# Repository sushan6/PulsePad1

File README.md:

# PulsePad

PulsePad is an ultra-compact, open-source 4-key macropad powered by the **Seeed Studio XIAO RP2040** microcontroller.

I wanted to make a small macropad with four mechanical switches that could be used for shortcuts and other frequently used actions. I designed the PCB and schematic in KiCad and also worked on a 3D enclosure to fit the board.

The design uses the XIAO RP2040 as the main controller, with four mechanical switches connected to it. The idea is to keep everything compact without making the PCB or enclosure unnecessarily complicated.

## Features

- 4 mechanical switches
- Seeed Studio XIAO RP2040 microcontroller
- Custom PCB designed in KiCad
- Custom 3D enclosure
- Compact design
- Open-source hardware

# 3D Model

This is the overall 3D model of PulsePad, showing how the PCB, switches, keycaps, and enclosure fit together.

# 3D Front View of PCB

# 3D Back View of PCB

# PCB

The PCB contains the four mechanical switch positions and the footprint for the XIAO RP2040. I designed the layout in KiCad and arranged the components to keep the board as compact as possible.

# Schematics

The schematic shows the connections between the four mechanical switches and the XIAO RP2040.

# How It Works

The XIAO RP2040 is responsible for reading the inputs from the four mechanical switches.

Each switch is connected to a GPIO pin on the microcontroller. When a key is pressed, the RP2040 can detect the input and the firmware can use it to trigger a keyboard shortcut or another assigned action.

The keys can be configured for different functions depending on how the firmware is set up.

# Enclosure

I also designed a 3D enclosure for the PCB. It is made to fit the board and switches while keeping the overall size small.

The enclosure can be 3D printed and modified if any adjustments to the design are needed.

# Design Files

The project includes the KiCad schematic and PCB design files, along with the 3D model of the board and enclosure.

These files can be used to inspect the design, make changes, or manufacture your own PulsePad.

## Acknowledgements

This project was designed using **KiCad EDA**. Thanks to the KiCad developers and the open-source community for making such a useful tool available for hardware design.

---

## License

This project is open-source. Feel free to modify, manufacture, and adapt it for your own personal use!

---

## Bill of Materials (BOM)

The following table contains the components required to build one PulsePad, along with their footprints, quantities, purchase links, and estimated prices.

## Bill of Materials (BOM)

### Main BOM

| **Item** | **Link** | **Quantity** | **Cost (USD)** | **Notes** |
|---|---|---:|---:|---|
| Seeed Studio XIAO RP2040 | [Robu.in](https://robu.in/product/seeed-studio-xiao-rp2040-v1-0/) | 2 | $13 | $6.5 each |
| Mechanical switches | [Amazon.in](https://www.amazon.in/dp/B0HJYNT2W7) | 1 pack | $7 | Pack of 40 |
| Gradient keycaps | [Amazon.in](https://www.amazon.in/dp/B0HGLWF4Q1) | 1 pack | $11 | 133-piece set |
| Custom PCB | [JLCPCB](https://jlcpcb.com/) | 5 | $12.00 | PCB fabrication |
| Enclosures | N/A | 5 | $0.00 | Self-printed |

### Cost Summary

| **Item** | **Cost (USD)** |
|---|---:|     
| XIAO RP2040 | $13 |
| Mechanical switches | $7 |
| Gradient keycaps | $11 |
| PCB fabrication | $12.00 |
| Enclosures | $0.00 |
| **Total** | **$43** |

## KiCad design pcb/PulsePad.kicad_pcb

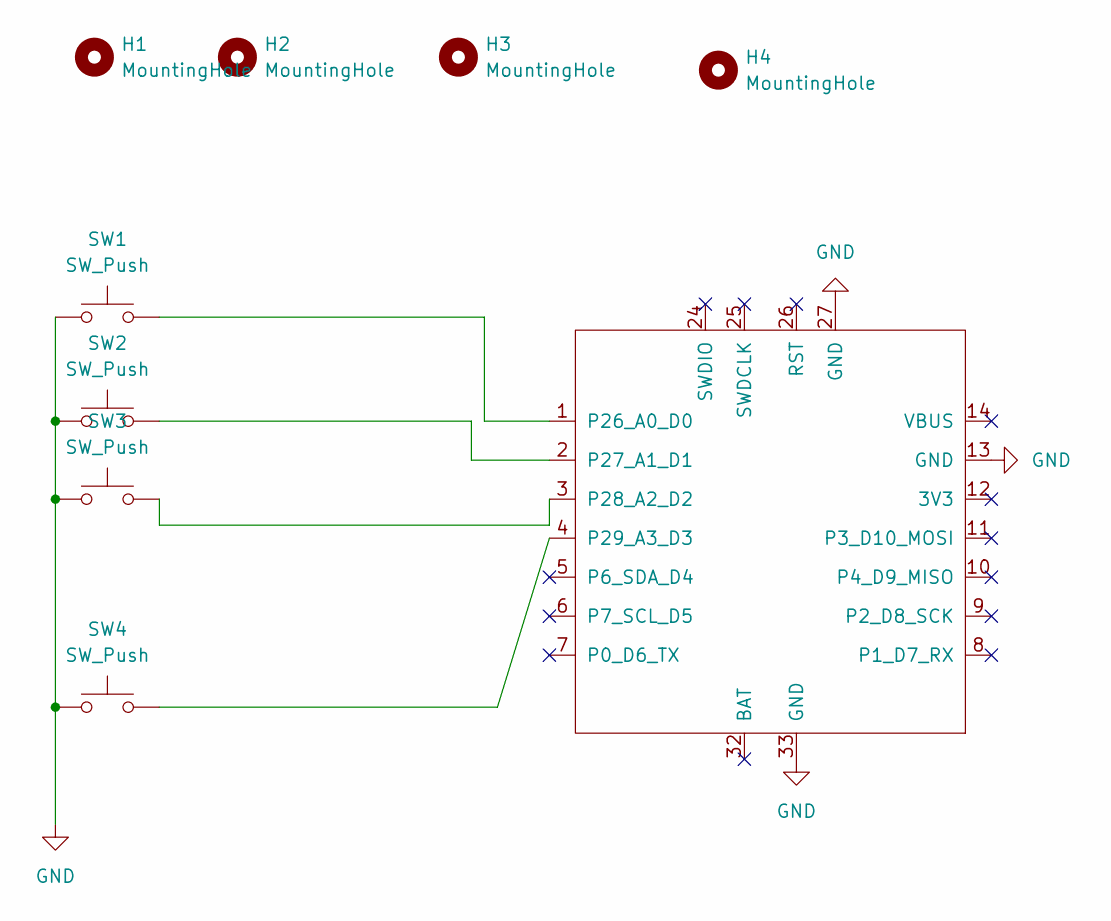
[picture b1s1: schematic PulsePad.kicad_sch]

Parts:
H1, H2, H3, H4: MountingHole; MountingHole_2.1mm
SW1, SW2, SW3, SW4: SW_Push; SW_Cherry_MX_1.00u_PCB
U1: XIAO-RP2040-SMD; XIAO-RP2040-SMD (1)

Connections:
GND: SW1.1, SW2.1, SW3.1, SW4.1, U1.13 (GND), U1.27 (GND), U1.33 (GND)
unnamed: SW1.2, U1.1 (P26_A0_D0)
unnamed: SW2.2, U1.2 (P27_A1_D1)
unnamed: SW3.2, U1.3 (P28_A2_D2)
unnamed: SW4.2, U1.4 (P29_A3_D3)

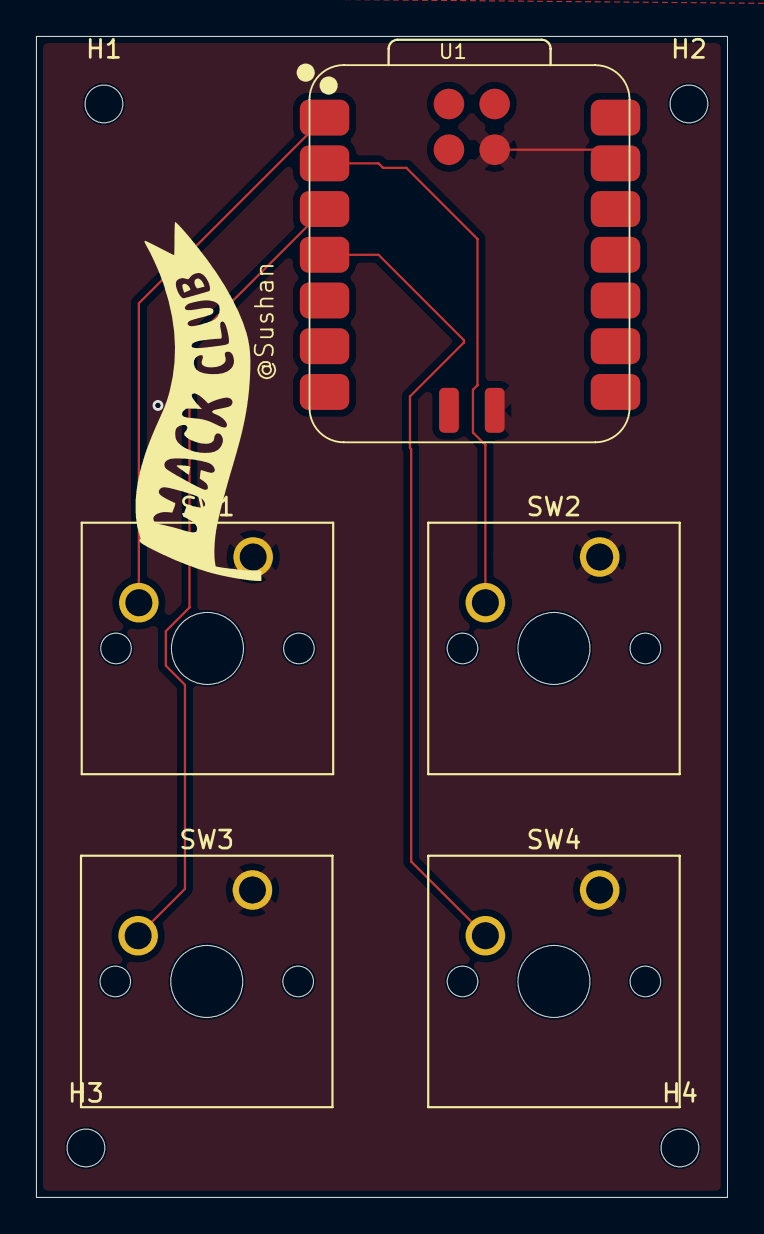
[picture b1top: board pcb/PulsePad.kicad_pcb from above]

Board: 4 copper layers, 38.4 x 64.5 mm, 9 parts (0 on the bottom side), 5 nets.

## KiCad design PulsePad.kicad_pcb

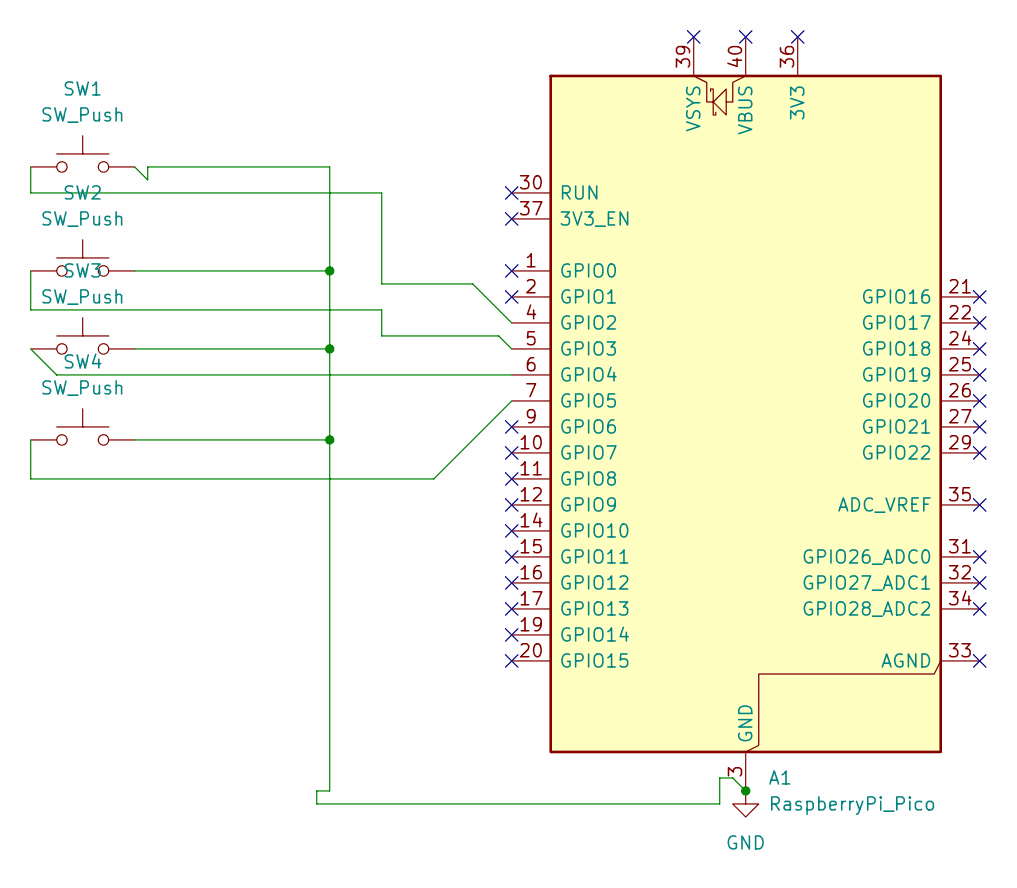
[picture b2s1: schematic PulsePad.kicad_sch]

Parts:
A1: RaspberryPi_Pico; RaspberryPi_Pico_Common_Unspecified
SW1, SW2, SW3, SW4: SW_Push; SW_Cherry_MX_1.00u_PCB

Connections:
GND: A1.3 (GND), A1.8 (GND), A1.13 (GND), A1.18 (GND), A1.23 (GND), A1.28 (GND), A1.38 (GND), SW1.2, SW2.2, SW3.2, SW4.2
unnamed: A1.4 (GPIO2), SW1.1
unnamed: A1.5 (GPIO3), SW2.1
unnamed: A1.6 (GPIO4), SW3.1
unnamed: A1.7 (GPIO5), SW4.1

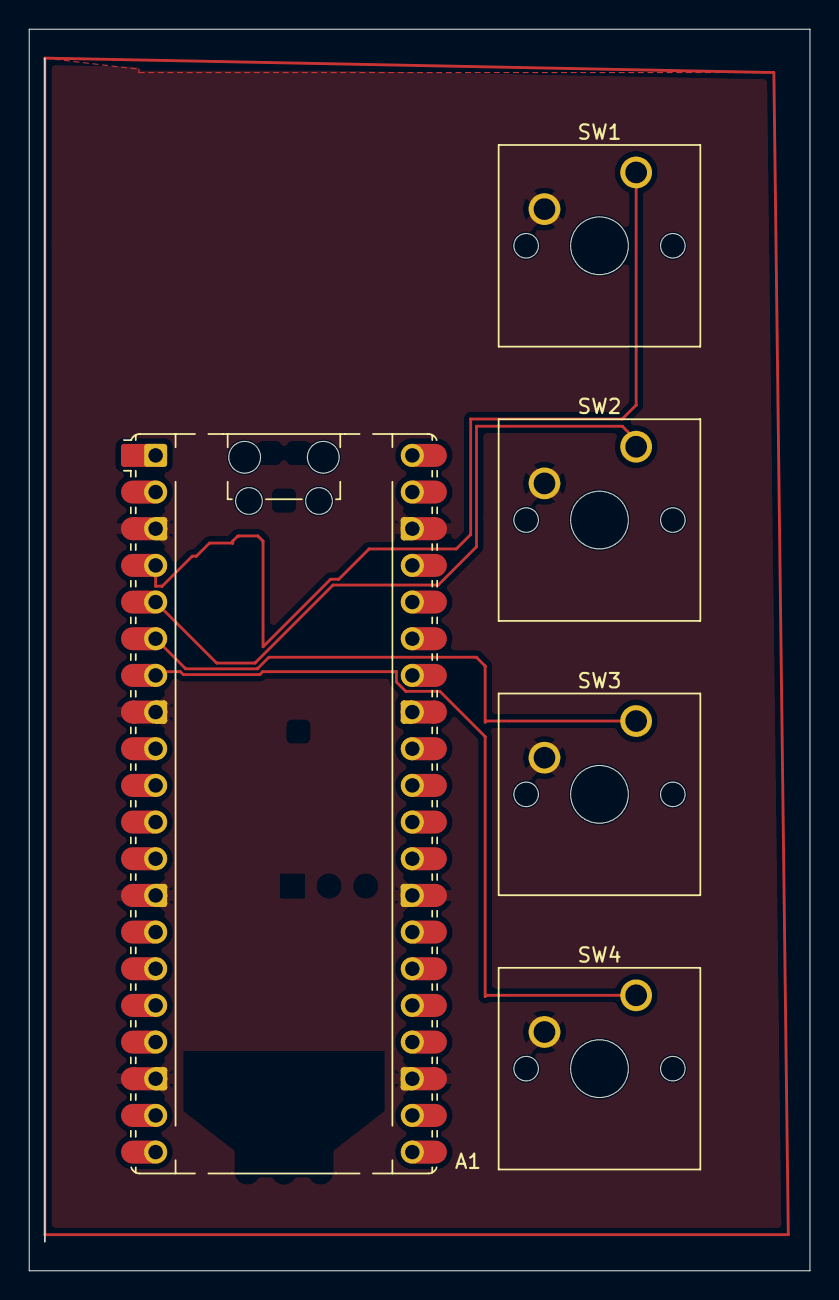
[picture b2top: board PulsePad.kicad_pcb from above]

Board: 4 copper layers, 54.1 x 86.0 mm, 5 parts (0 on the bottom side), 5 nets.

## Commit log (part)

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2026-05-29 Update README with images and project details
    Added images and improved project description.
2026-06-28 Adding FIles
2026-06-28 Enhance README with project details and acknowledgements
    Expanded description of PulsePad and added acknowledgements and license sections.
